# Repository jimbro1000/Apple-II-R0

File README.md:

# APPLE II R0 Reproduction #

## Goal
THe primary goal is to have an accurate KiCAD schematic of the 
Apple II Revision 0 System Board. This is supplemented with a
complete reproduction PCB that can be fabricated.

## Apple II R0 Notes

This schematic was taken from the [BitPreserve project](https://github.com/baldengineer/bit-preserve) and compared to the Apple II Gerbers by Mike Willegal (http://www.willegal.net/appleii/appleii-first_page.htm).
When necessary, The Apple II Circuit Description by Winston D. Gayler was consulted.

The PCB layout is a reworking of the Gerbers by Mike Willegal in 
KiCad. Where components are unobtainable from regular suppliers,
substitutes have been used with part number references.

## Current Status

1) Some errors have been found and corrected.
2) Additional work needs to be done to clean-up the schematic.
3) PCB is fully routed but needs mounting holes placing
4) Labelling (silkscreen) on the PCB is messy and needs cleaning up

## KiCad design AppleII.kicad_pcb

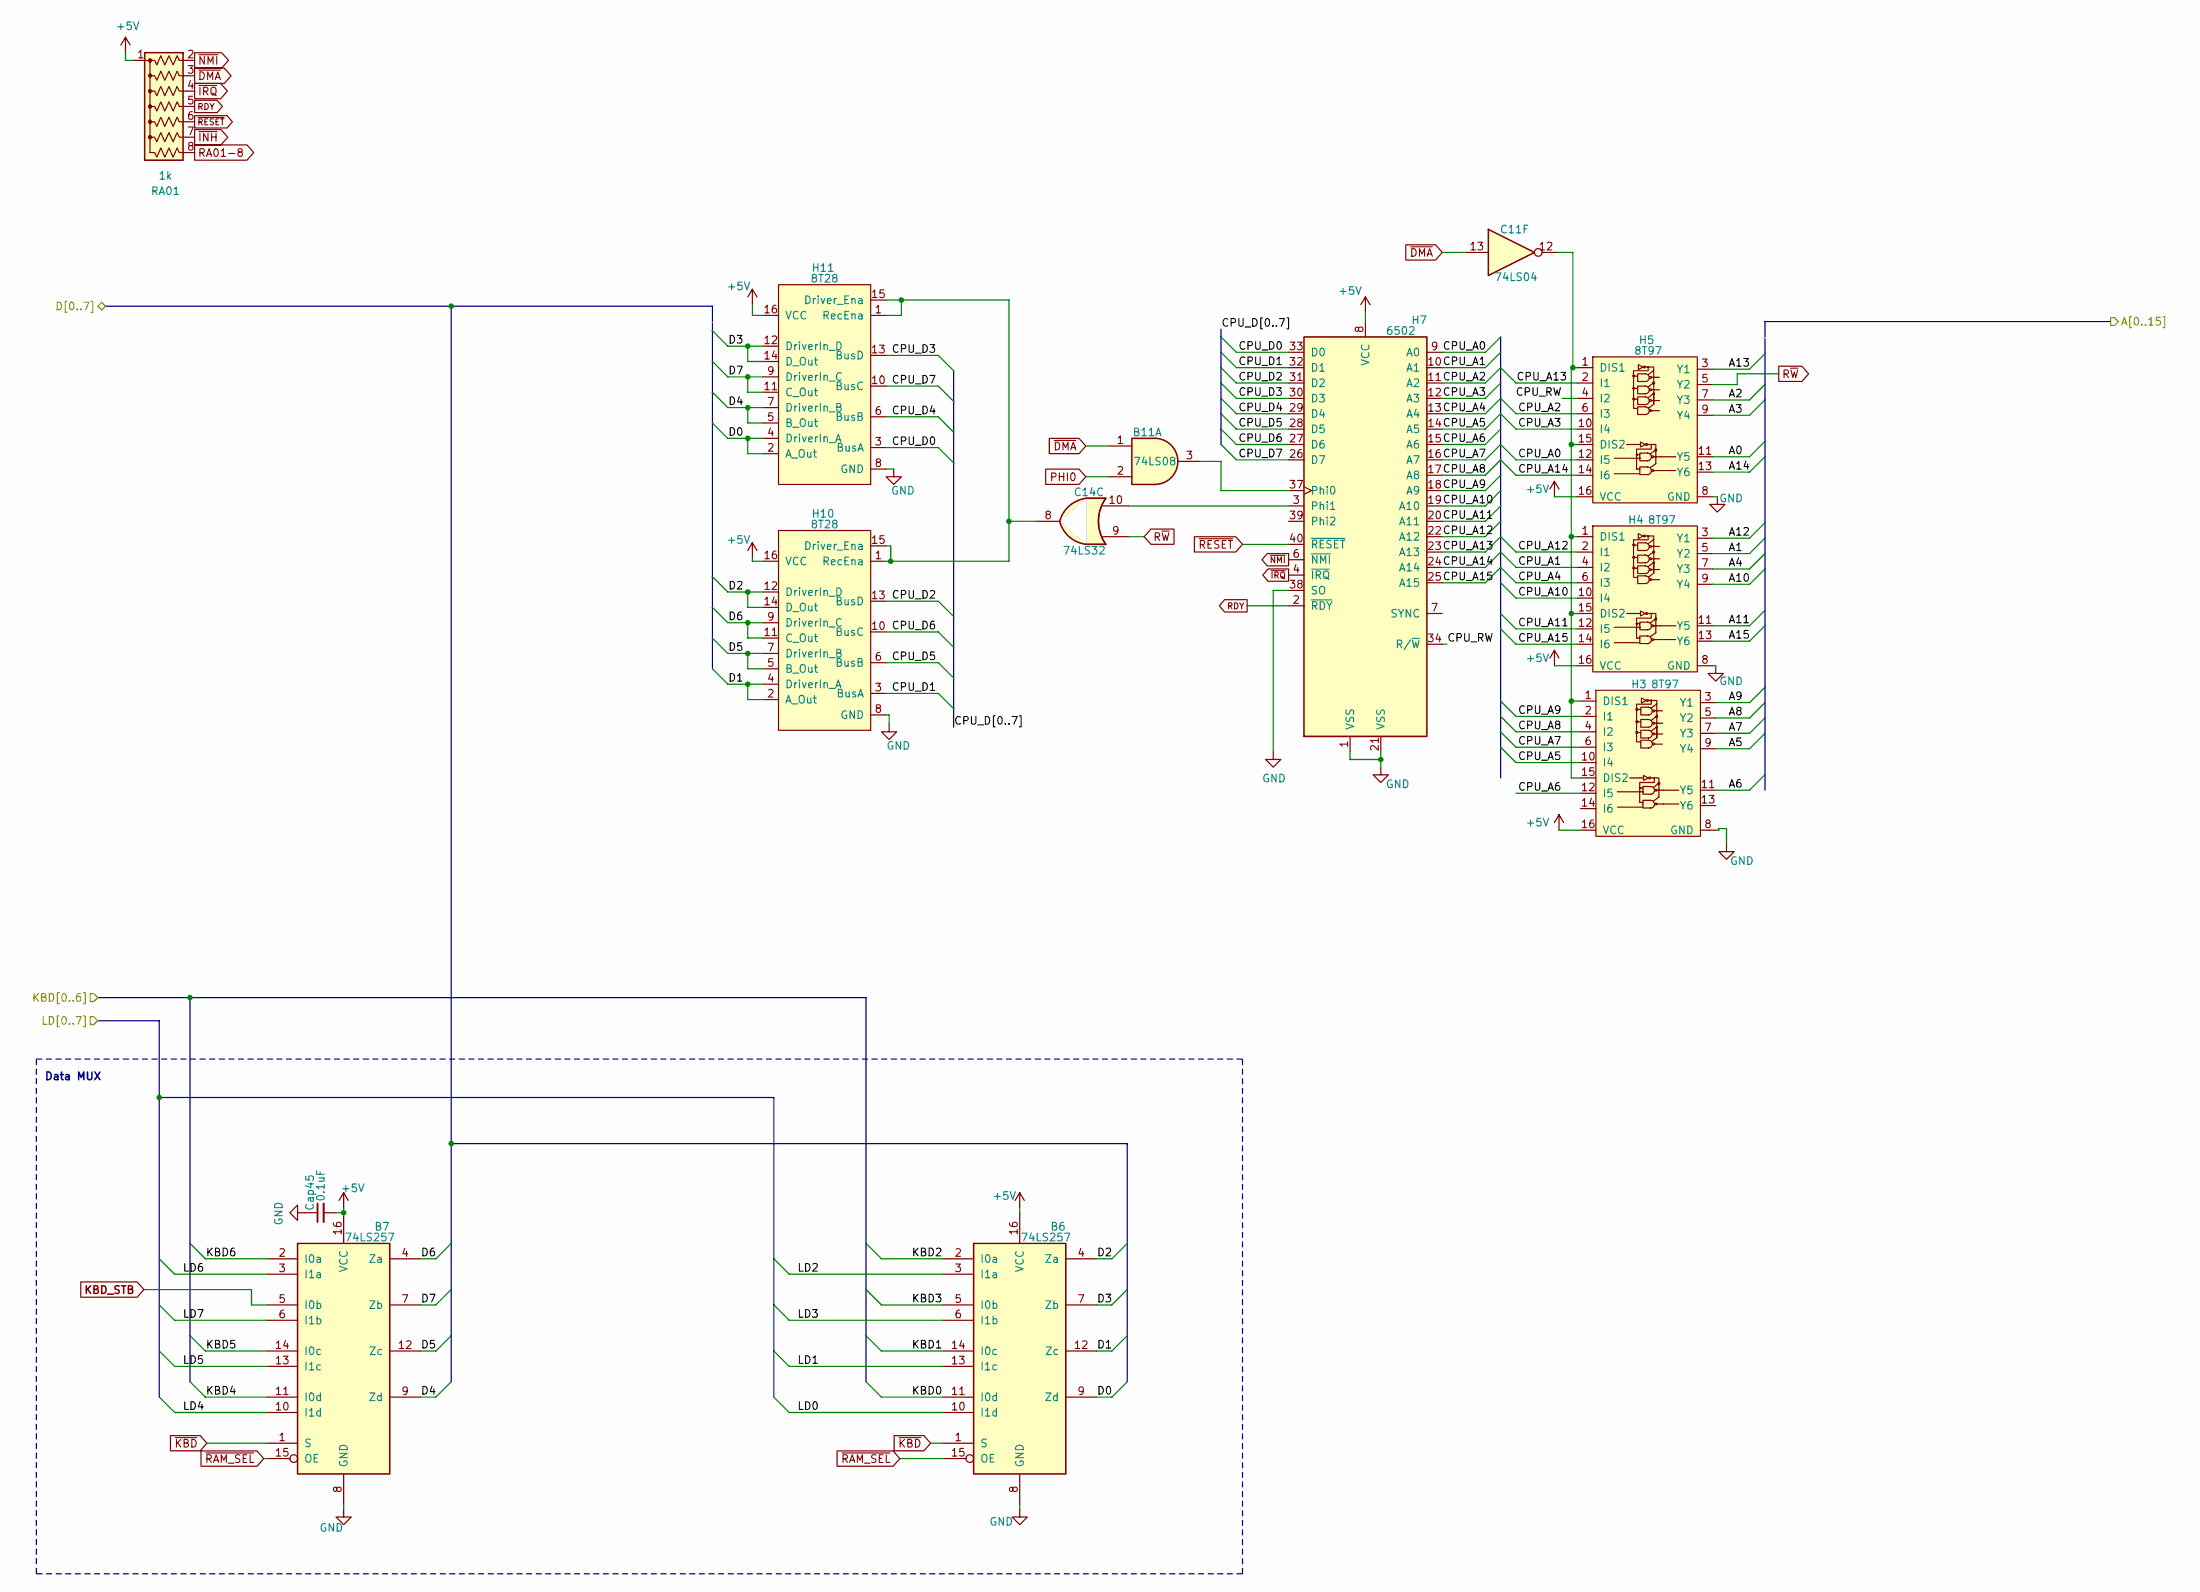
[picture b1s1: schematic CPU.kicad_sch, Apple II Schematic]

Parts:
B6, B7: 74LS257; DIP-16_W7.62mm
B11: 74LS08; DIP-14_W7.62mm
C11: 74LS04; DIP-14_W7.62mm
C14: 74LS32; DIP-14_W7.62mm
Cap45: 0.1uF; C_Disc_D5.0mm_W2.5mm_P5.00mm
H3, H4, H5: 8T97; DIP-16_W7.62mm
H7: 6502; DIP-40_W15.24mm
H10, H11: 8T28; DIP-16_W7.62mm
RA01: 1k; R_Array_SIP8

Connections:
+5V: B6.16 (VCC), B7.16 (VCC), Cap45.2, H3.16 (VCC), H4.16 (VCC), H5.16 (VCC), H7.8 (VCC), H10.16 (VCC), H11.16 (VCC), RA01.1 (common); also elsewhere on the board
/Address Decoder and Onboard IO/KBD0: B6.11 (I0d); also elsewhere on the board
/Address Decoder and Onboard IO/KBD1: B6.14 (I0c); also elsewhere on the board
/Address Decoder and Onboard IO/KBD2: B6.2 (I0a); also elsewhere on the board
/Address Decoder and Onboard IO/KBD3: B6.5 (I0b); also elsewhere on the board
/Address Decoder and Onboard IO/KBD4: B7.11 (I0d); also elsewhere on the board
/Address Decoder and Onboard IO/KBD5: B7.14 (I0c); also elsewhere on the board
/Address Decoder and Onboard IO/KBD6: B7.2 (I0a); also elsewhere on the board
/CPU Tranceiver Driver and Data MUX/CPU_A0: H5.12 (I5), H7.9 (A0)
/CPU Tranceiver Driver and Data MUX/CPU_A1: H4.4 (I2), H7.10 (A1)
/CPU Tranceiver Driver and Data MUX/CPU_A2: H5.6 (I3), H7.11 (A2)
/CPU Tranceiver Driver and Data MUX/CPU_A3: H5.10 (I4), H7.12 (A3)
/CPU Tranceiver Driver and Data MUX/CPU_A4: H4.6 (I3), H7.13 (A4)
/CPU Tranceiver Driver and Data MUX/CPU_A5: H3.10 (I4), H7.14 (A5)
/CPU Tranceiver Driver and Data MUX/CPU_A6: H3.12 (I5), H7.15 (A6)
/CPU Tranceiver Driver and Data MUX/CPU_A7: H3.6 (I3), H7.16 (A7)
/CPU Tranceiver Driver and Data MUX/CPU_A8: H3.4 (I2), H7.17 (A8)
/CPU Tranceiver Driver and Data MUX/CPU_A9: H3.2 (I1), H7.18 (A9)
/CPU Tranceiver Driver and Data MUX/CPU_A10: H4.10 (I4), H7.19 (A10)
/CPU Tranceiver Driver and Data MUX/CPU_A11: H4.12 (I5), H7.20 (A11)
/CPU Tranceiver Driver and Data MUX/CPU_A12: H4.2 (I1), H7.22 (A12)
/CPU Tranceiver Driver and Data MUX/CPU_A13: H5.2 (I1), H7.23 (A13)
/CPU Tranceiver Driver and Data MUX/CPU_A14: H5.14 (I6), H7.24 (A14)
/CPU Tranceiver Driver and Data MUX/CPU_A15: H4.14 (I6), H7.25 (A15)
/CPU Tranceiver Driver and Data MUX/CPU_D0: H7.33 (D0), H11.3 (BusA)
/CPU Tranceiver Driver and Data MUX/CPU_D1: H7.32 (D1), H10.3 (BusA)
/CPU Tranceiver Driver and Data MUX/CPU_D2: H7.31 (D2), H10.13 (BusD)
/CPU Tranceiver Driver and Data MUX/CPU_D3: H7.30 (D3), H11.13 (BusD)
/CPU Tranceiver Driver and Data MUX/CPU_D4: H7.29 (D4), H11.6 (BusB)
/CPU Tranceiver Driver and Data MUX/CPU_D5: H7.28 (D5), H10.6 (BusB)
/CPU Tranceiver Driver and Data MUX/CPU_D6: H7.27 (D6), H10.10 (BusC)
/CPU Tranceiver Driver and Data MUX/CPU_D7: H7.26 (D7), H11.10 (BusC)
/CPU Tranceiver Driver and Data MUX/CPU_RW: H5.4 (I2), H7.34 (R/~W)
/CPU Tranceiver Driver and Data MUX/LD0: B6.10 (I1d); also elsewhere on the board
/CPU Tranceiver Driver and Data MUX/LD1: B6.13 (I1c); also elsewhere on the board
/CPU Tranceiver Driver and Data MUX/LD2: B6.3 (I1a); also elsewhere on the board
/CPU Tranceiver Driver and Data MUX/LD3: B6.6 (I1b); also elsewhere on the board
/CPU Tranceiver Driver and Data MUX/LD4: B7.10 (I1d); also elsewhere on the board
/CPU Tranceiver Driver and Data MUX/LD5: B7.13 (I1c); also elsewhere on the board
/CPU Tranceiver Driver and Data MUX/LD6: B7.3 (I1a); also elsewhere on the board
/CPU Tranceiver Driver and Data MUX/LD7: B7.6 (I1b); also elsewhere on the board
A0: H5.11 (Y5); also elsewhere on the board
A1: H4.5 (Y2); also elsewhere on the board
A2: H5.7 (Y3); also elsewhere on the board
A3: H5.9 (Y4); also elsewhere on the board
A4: H4.7 (Y3); also elsewhere on the board
A5: H3.9 (Y4); also elsewhere on the board
A6: H3.11 (Y5); also elsewhere on the board
A7: H3.7 (Y3); also elsewhere on the board
A8: H3.5 (Y2); also elsewhere on the board
A9: H3.3 (Y1); also elsewhere on the board
A10: H4.9 (Y4); also elsewhere on the board
A11: H4.11 (Y5); also elsewhere on the board
A12: H4.3 (Y1); also elsewhere on the board
A13: H5.3 (Y1); also elsewhere on the board
A14: H5.13 (Y6); also elsewhere on the board
A15: H4.13 (Y6); also elsewhere on the board
D0: B6.9 (Zd), H11.2 (A_Out), H11.4 (DriverIn_A); also elsewhere on the board
D1: B6.12 (Zc), H10.2 (A_Out), H10.4 (DriverIn_A); also elsewhere on the board
D2: B6.4 (Za), H10.12 (DriverIn_D), H10.14 (D_Out); also elsewhere on the board
D3: B6.7 (Zb), H11.12 (DriverIn_D), H11.14 (D_Out); also elsewhere on the board
D4: B7.9 (Zd), H11.5 (B_Out), H11.7 (DriverIn_B); also elsewhere on the board
D5: B7.12 (Zc), H10.5 (B_Out), H10.7 (DriverIn_B); also elsewhere on the board
D6: B7.4 (Za), H10.9 (DriverIn_C), H10.11 (C_Out); also elsewhere on the board
D7: B7.7 (Zb), H11.9 (DriverIn_C), H11.11 (C_Out); also elsewhere on the board
GND: B6.8 (GND), B7.8 (GND), Cap45.1, H3.8 (GND), H4.8 (GND), H5.8 (GND), H7.1 (VSS), H7.21 (VSS), H7.38 (SO), H10.8 (GND), H11.8 (GND); also elsewhere on the board
KBD_STB: B7.5 (I0b); also elsewhere on the board
unnamed: C11.12, H3.1 (DIS1), H3.15 (DIS2), H4.1 (DIS1), H4.15 (DIS2), H5.1 (DIS1), H5.15 (DIS2)
unnamed: B11.3, H7.37 (Phi0)
unnamed: C14.10, H7.3 (Phi1)
unnamed: C14.8, H10.1 (RecEna), H10.15 (Driver_Ena), H11.1 (RecEna), H11.15 (Driver_Ena)
PHI0: B11.2; also elsewhere on the board
RA01-8: RA01.8 (R7); also elsewhere on the board
RDY: H7.2 (~RDY), RA01.5 (R4); also elsewhere on the board
R~W: C14.9, H5.5 (Y2); also elsewhere on the board
~DMA: B11.1, C11.13, RA01.3 (R2); also elsewhere on the board
~INH: RA01.7 (R6); also elsewhere on the board
~IRQ: H7.4 (~IRQ), RA01.4 (R3); also elsewhere on the board
~KBD: B6.1 (S), B7.1 (S); also elsewhere on the board
~NMI: H7.6 (~NMI), RA01.2 (R1); also elsewhere on the board
~RAM_SEL: B6.15 (OE), B7.15 (OE); also elsewhere on the board
~RESET: H7.40 (~RESET), RA01.6 (R5); also elsewhere on the board

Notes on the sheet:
Data MUX

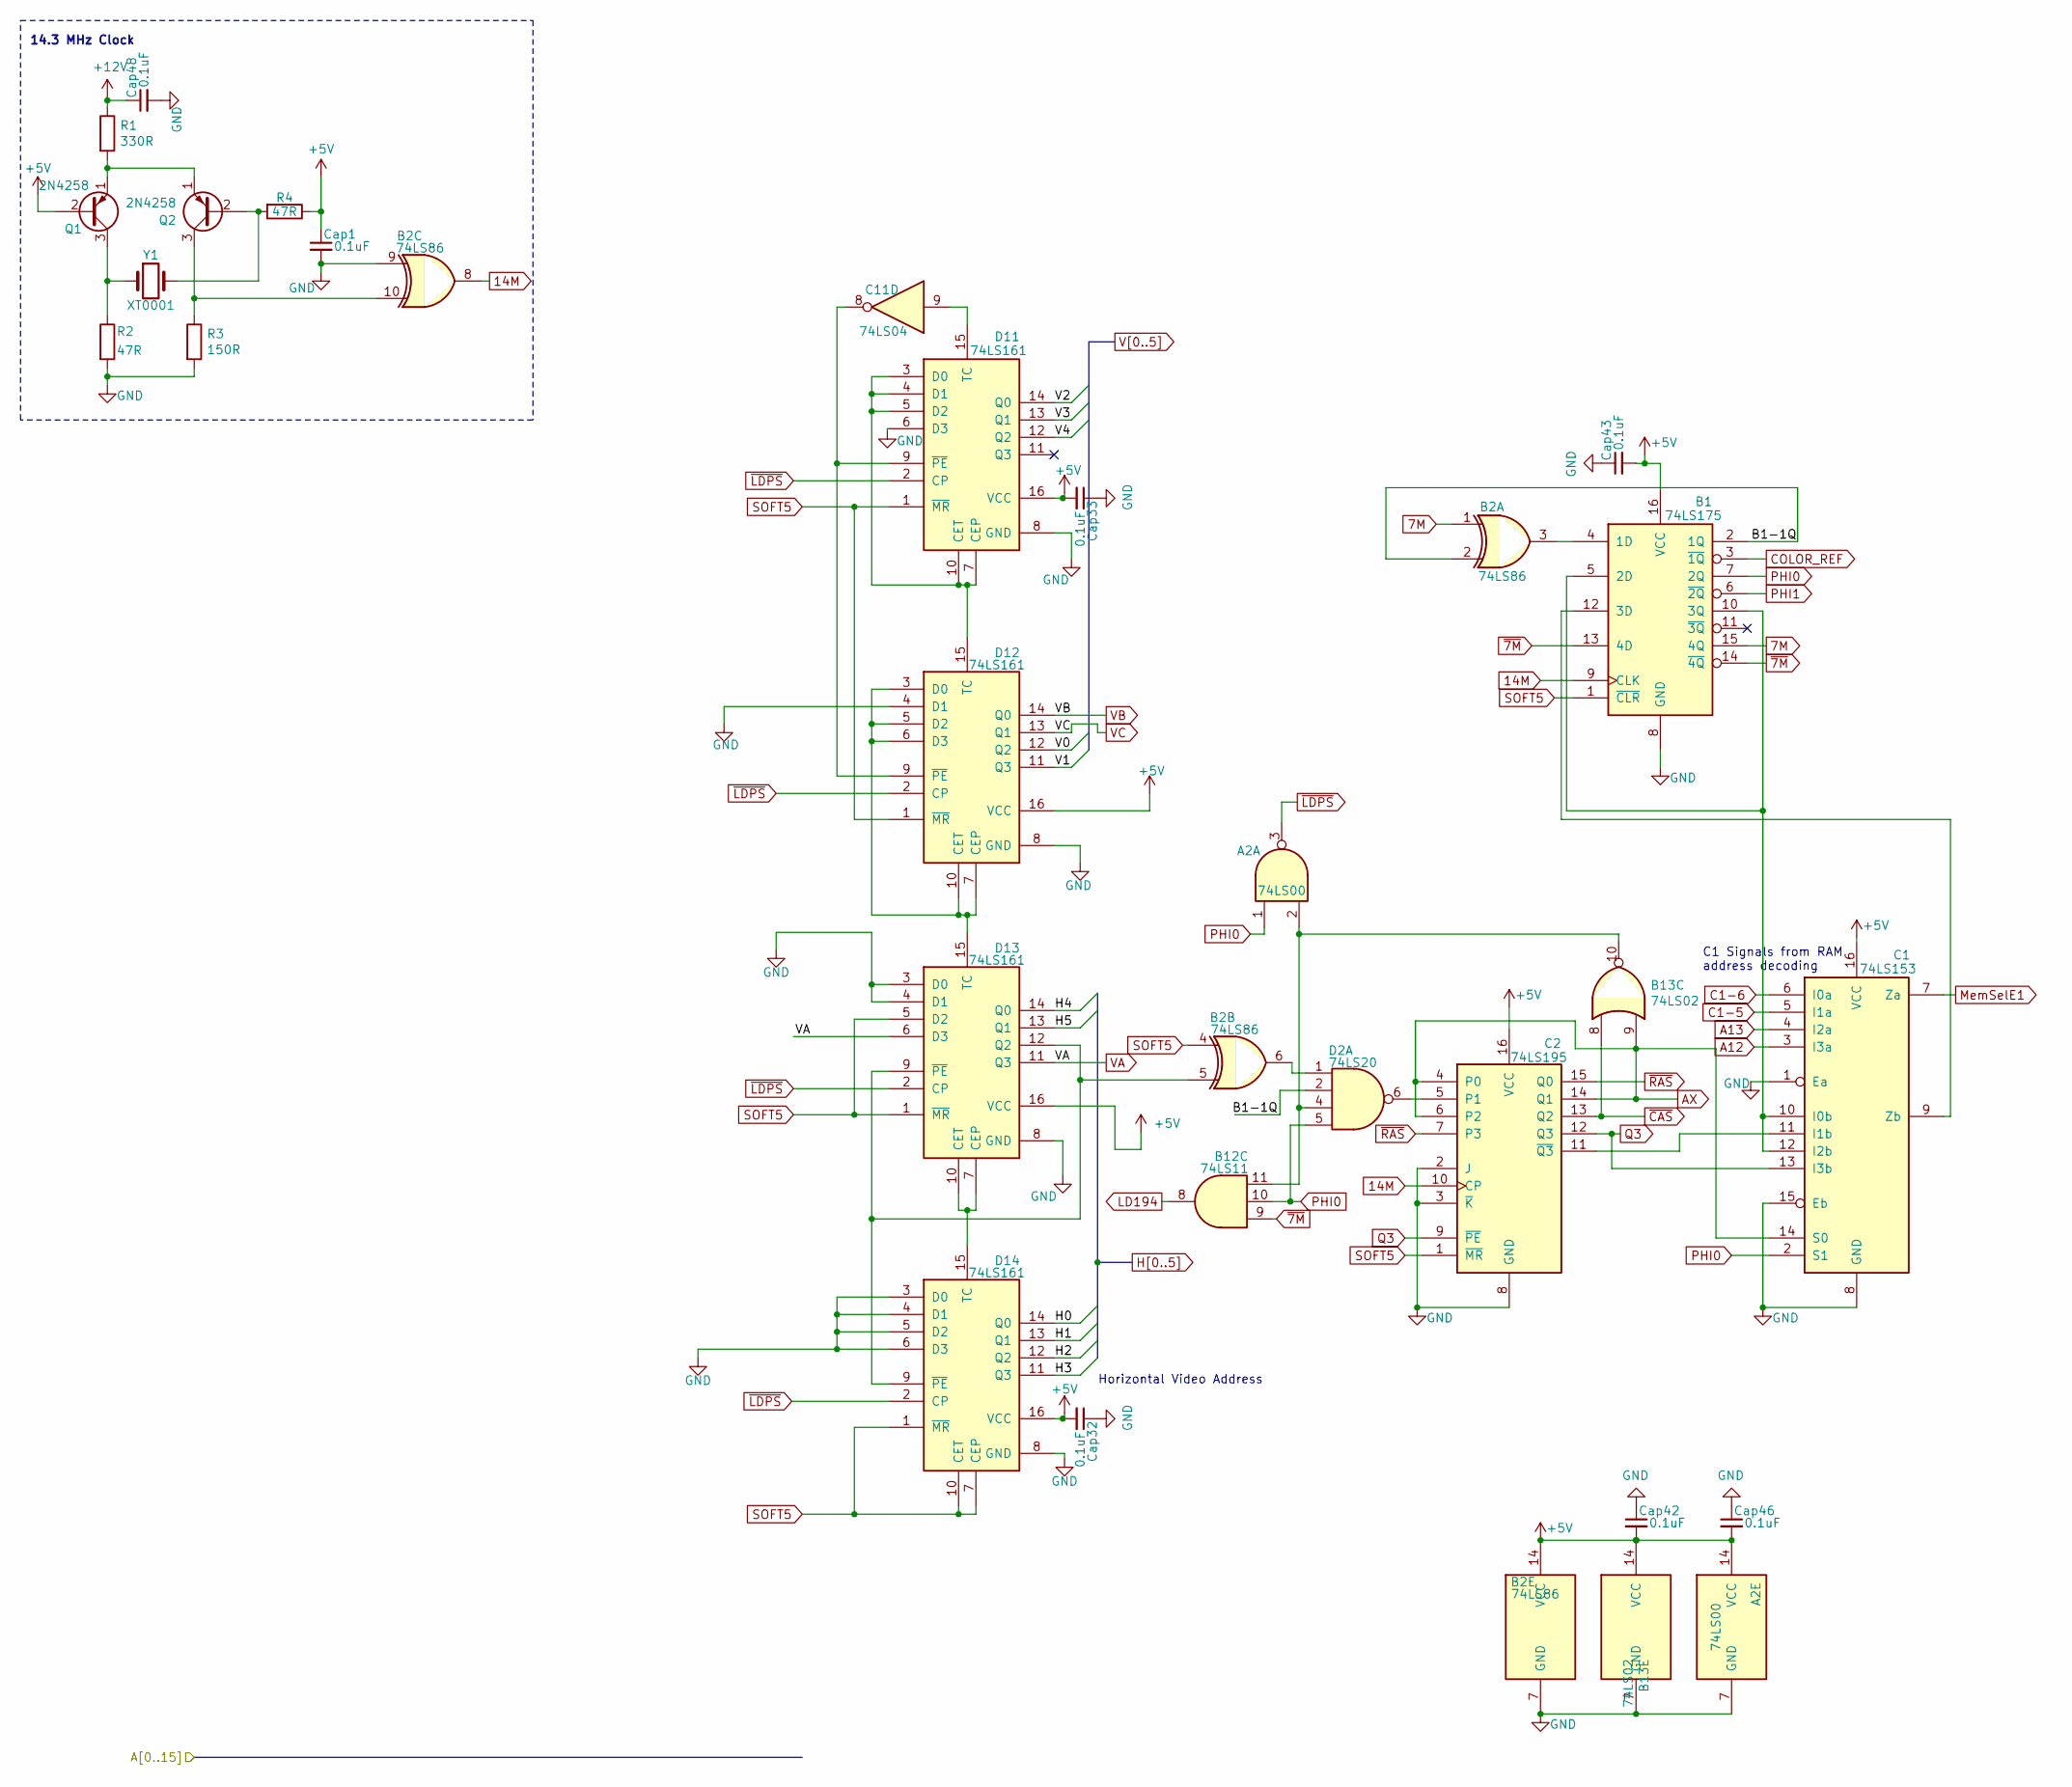
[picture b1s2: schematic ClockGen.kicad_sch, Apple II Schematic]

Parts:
A2: 74LS00; DIP-14_W7.62mm
B1: 74LS175; DIP-16_W7.62mm
B2: 74LS86; DIP-14_W7.62mm
B12: 74LS11; DIP-14_W7.62mm
B13: 74LS02; DIP-14_W7.62mm
C1: 74LS153; DIP-16_W7.62mm
C2: 74LS195; DIP-16_W7.62mm
C11: 74LS04; DIP-14_W7.62mm
Cap1, Cap32, Cap33, Cap42, Cap43, Cap46, Cap48: 0.1uF; C_Disc_D5.0mm_W2.5mm_P5.00mm
D2: 74LS20; DIP-14_W7.62mm
D11, D12, D13, D14: 74LS161; DIP-16_W7.62mm
Q1, Q2: 2N4258; TO-18-3; DigiKey 2N4208-ND
R1: 330R; R_Axial_DIN0207_L6.3mm_D2.5mm_P10.16mm_Horizontal
R2, R4: 47R; R_Axial_DIN0207_L6.3mm_D2.5mm_P10.16mm_Horizontal
R3: 150R; R_Axial_DIN0207_L6.3mm_D2.5mm_P10.16mm_Horizontal
Y1: XT0001; Crystal_HC18-U_Vertical

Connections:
7M: B1.15 (4Q), B2.1; also elsewhere on the board
14M: B1.9 (CLK), B2.8, C2.10 (CP); also elsewhere on the board
+5V: A2.14 (VCC), B1.16 (VCC), B2.14 (VCC), B13.14 (VCC), C1.16 (VCC), C2.16 (VCC), Cap1.1, Cap32.2, Cap33.2, Cap42.2, Cap43.2, Cap46.2, D11.16 (VCC), D12.16 (VCC), D13.16 (VCC), D14.16 (VCC), Q1.2 (B), R4.1; also elsewhere on the board
+12V: Cap48.1, R1.1; also elsewhere on the board
/Clock Generation/B1-1Q: B1.2 (1Q), B2.2, D2.2
/Clock Generation/H0: D14.14 (Q0); also elsewhere on the board
/Clock Generation/H1: D14.13 (Q1); also elsewhere on the board
/Clock Generation/H2: D14.12 (Q2); also elsewhere on the board
/Clock Generation/H3: D14.11 (Q3); also elsewhere on the board
/Clock Generation/H4: D13.14 (Q0); also elsewhere on the board
/Clock Generation/H5: D13.13 (Q1); also elsewhere on the board
/Clock Generation/V1: D12.11 (Q3); also elsewhere on the board
/Clock Generation/V2: D11.14 (Q0); also elsewhere on the board
/Clock Generation/V3: D11.13 (Q1); also elsewhere on the board
/Clock Generation/V4: D11.12 (Q2); also elsewhere on the board
A12: C1.3 (I3a); also elsewhere on the board
A13: C1.4 (I2a); also elsewhere on the board
AX: B13.9, C1.14 (S0), C2.4 (P0), C2.6 (P2), C2.14 (Q1); also elsewhere on the board
C1-5: C1.5 (I1a); also elsewhere on the board
C1-6: C1.6 (I0a); also elsewhere on the board
COLOR_REF: B1.3 (~1Q); also elsewhere on the board
GND: A2.7 (GND), B1.8 (GND), B2.7 (GND), B2.9, B13.7 (GND), C1.1 (Ea), C1.8 (GND), C1.15 (Eb), C2.2 (J), C2.3 (~K), C2.8 (GND), Cap1.2, Cap32.1, Cap33.1, Cap42.1, Cap43.1, Cap46.1, Cap48.2, D11.6 (D3), D11.8 (GND), D12.4 (D1), D12.8 (GND), D13.3 (D0), D13.4 (D1), D13.8 (GND), D14.3 (D0), D14.4 (D1), D14.5 (D2), D14.6 (D3), D14.8 (GND), R2.2, R3.2; also elsewhere on the board
LD194: B12.8; also elsewhere on the board
MemSelE1: C1.7 (Za); also elsewhere on the board
unnamed: A2.2, B12.11, B13.10, D2.4
unnamed: B1.4 (1D), B2.3
unnamed: B1.5 (2D), B1.10 (3Q), C1.10 (I0b), C1.12 (I2b)
unnamed: B1.12 (3D), C1.9 (Zb)
unnamed: B2.6, D2.1
unnamed: C1.11 (I1b), C2.11 (~Q3)
unnamed: C2.5 (P1), D2.6
unnamed: D11.3 (D0), D11.4 (D1), D11.5 (D2), D11.7 (CEP), D11.10 (CET), D12.15 (TC)
unnamed: C11.9, D11.15 (TC)
unnamed: C11.8, D11.9 (~PE), D12.9 (~PE)
unnamed: D12.3 (D0), D12.5 (D2), D12.6 (D3), D12.7 (CEP), D12.10 (CET), D13.15 (TC)
unnamed: D13.7 (CEP), D13.10 (CET), D14.15 (TC)
unnamed: B2.5, D13.9 (~PE), D13.12 (Q2), D14.9 (~PE)
unnamed: Q1.3 (C), R2.1, Y1.1
unnamed: Q1.1 (E), Q2.1 (E), R1.2
unnamed: Q2.2 (B), R4.2, Y1.2
unnamed: B2.10, Q2.3 (C), R3.1
PHI0: A2.1, B1.7 (2Q), B12.10, C1.2 (S1), D2.5; also elsewhere on the board
PHI1: B1.6 (~2Q); also elsewhere on the board
Q3: C1.13 (I3b), C2.9 (~PE), C2.12 (Q3); also elsewhere on the board
SOFT5: B1.1 (~CLR), B2.4, C2.1 (~MR), D11.1 (~MR), D12.1 (~MR), D13.1 (~MR), D13.5 (D2), D14.1 (~MR), D14.7 (CEP), D14.10 (CET); also elsewhere on the board
V0: D12.12 (Q2); also elsewhere on the board
VA: D13.6 (D3), D13.11 (Q3); also elsewhere on the board
VB: D12.14 (Q0); also elsewhere on the board
VC: D12.13 (Q1); also elsewhere on the board
~7M: B1.13 (4D), B1.14 (~4Q), B12.9; also elsewhere on the board
~CAS: B13.8, C2.13 (Q2); also elsewhere on the board
~LDPS: A2.3, D11.2 (CP), D12.2 (CP), D13.2 (CP), D14.2 (CP); also elsewhere on the board
~RAS: C2.7 (P3), C2.15 (Q0); also elsewhere on the board

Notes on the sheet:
Horizontal Video Address
14.3 MHz Clock
C1 Signals from RAM address decoding

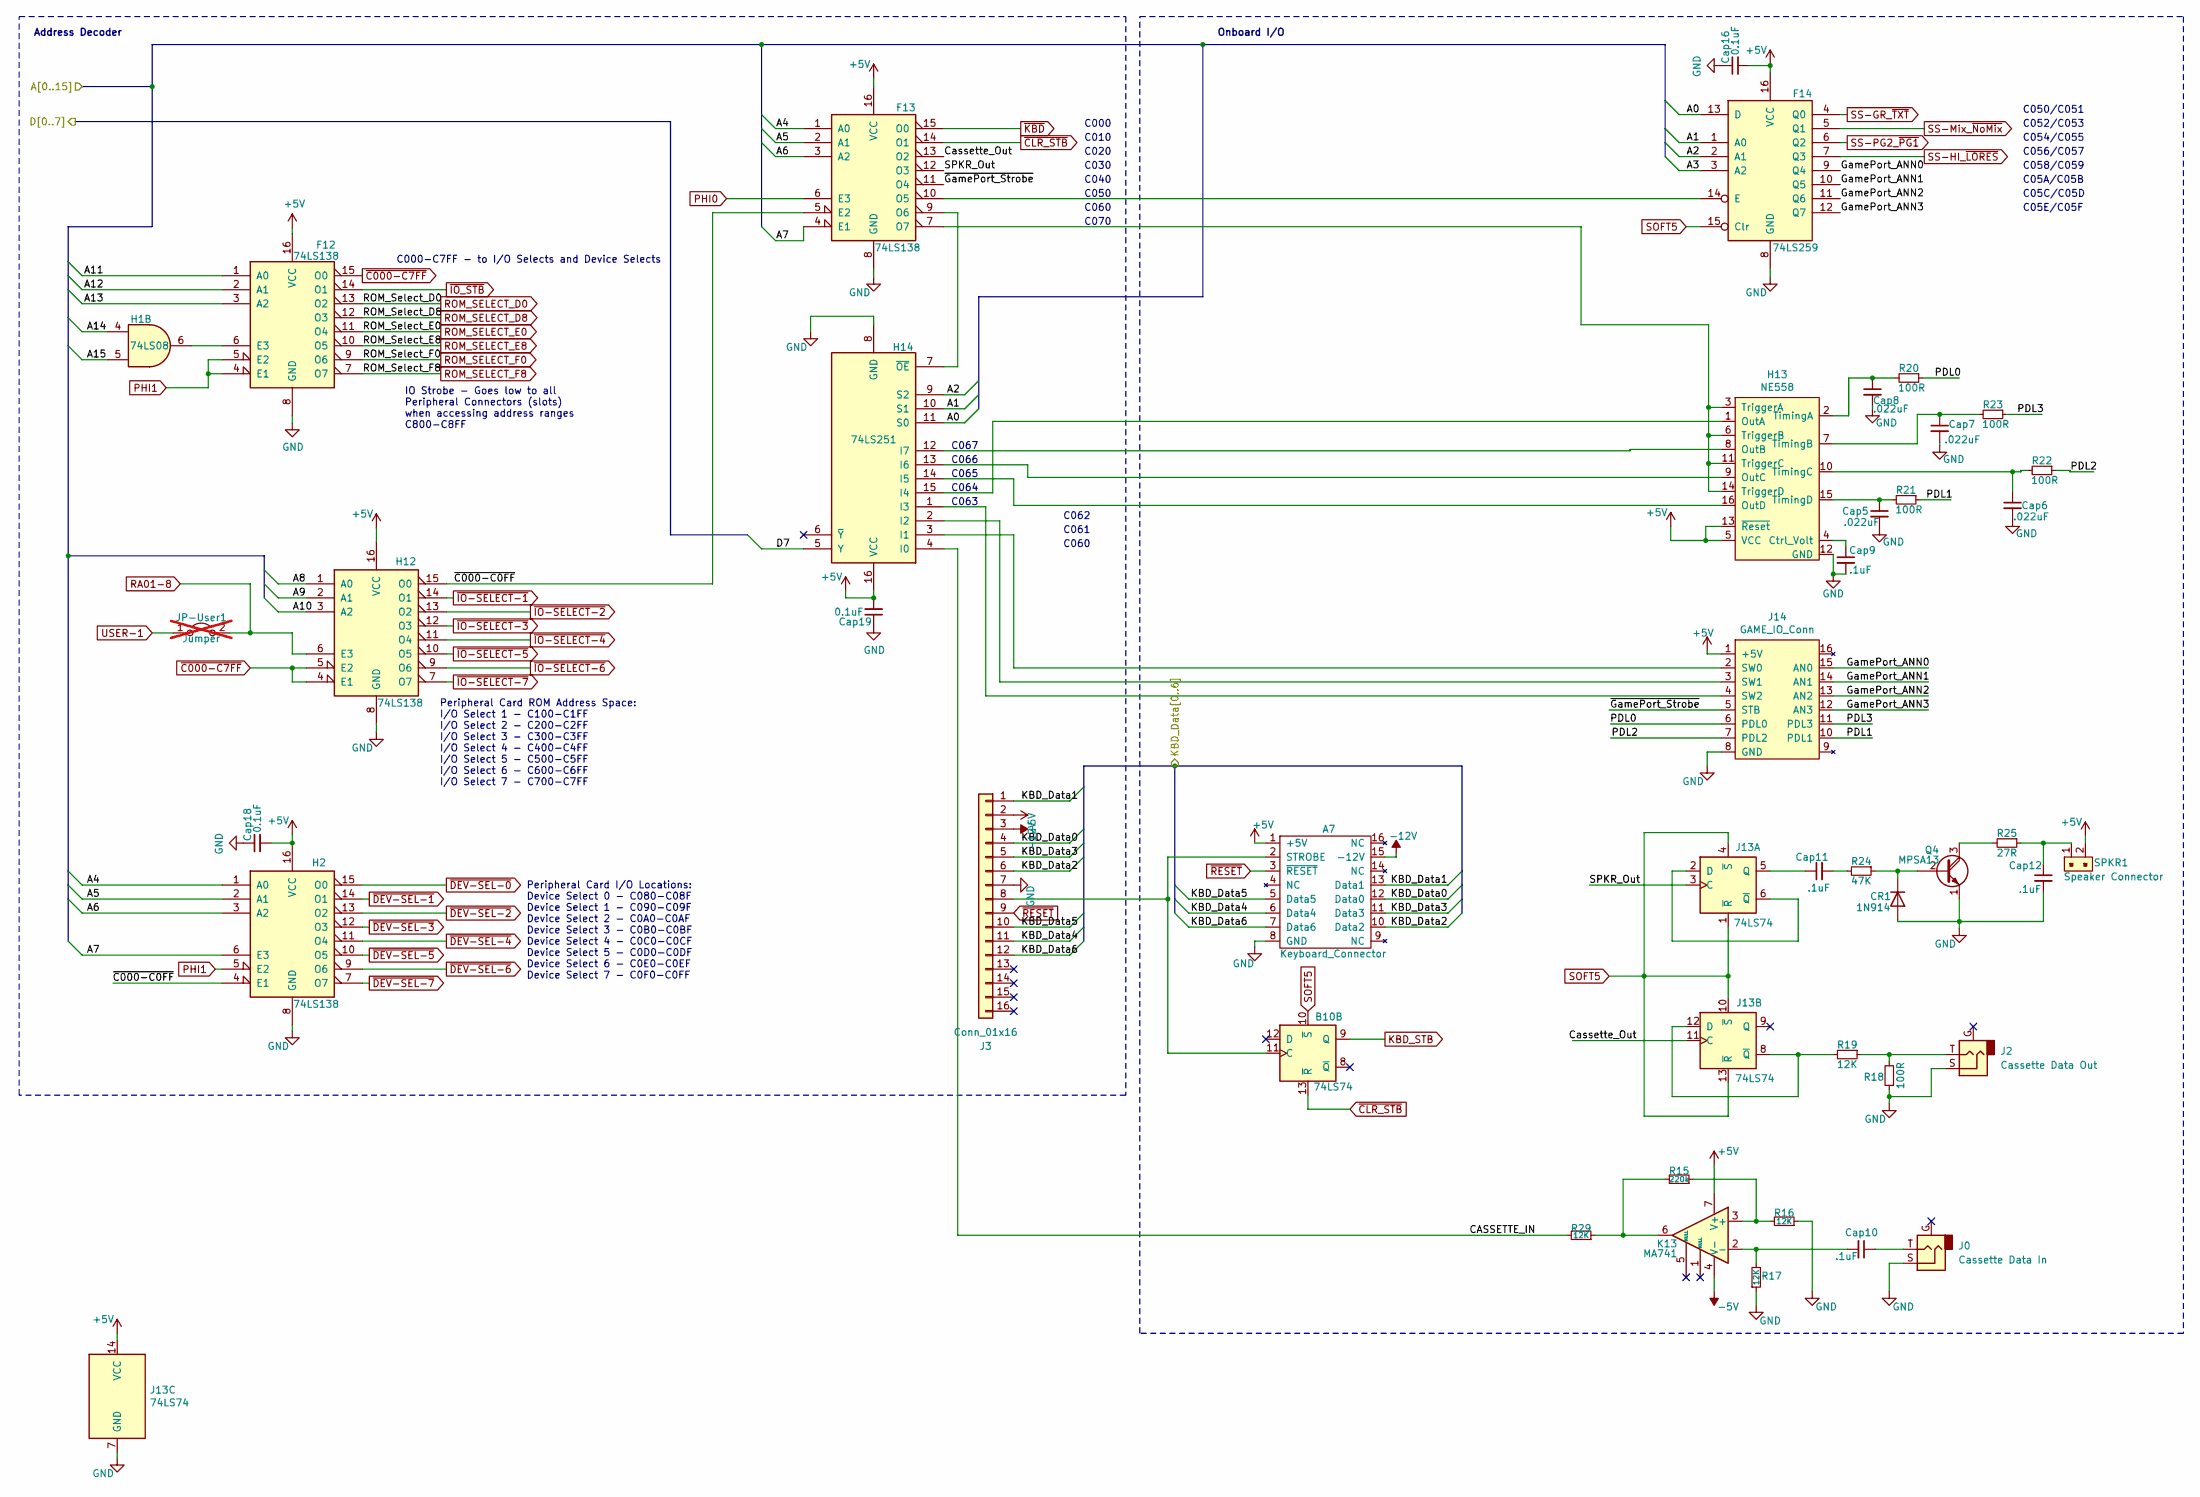
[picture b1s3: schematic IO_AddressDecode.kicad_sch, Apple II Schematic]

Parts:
A7: Keyboard_Connector; DIP-16_W7.62mm_Socket_LongPads
B10: 74LS74; DIP-14_W7.62mm
CR1: 1N914; D_DO-15_P10.16mm_Horizontal
Cap5, Cap6, Cap7, Cap8: .022uF; C_Disc_D5.0mm_W2.5mm_P5.00mm
Cap9, Cap10, Cap11, Cap12: .1uF; C_Disc_D5.0mm_W2.5mm_P5.00mm
Cap16, Cap18, Cap19: 0.1uF; C_Disc_D5.0mm_W2.5mm_P5.00mm
F12, F13: 74LS138; DIP-16_W7.62mm
F14: 74LS259; DIP-16_W7.62mm
H1: 74LS08; DIP-14_W7.62mm
H2, H12: 74LS138; DIP-16_W7.62mm
H13: NE558; DIP-16_W7.62mm
H14: 74LS251; DIP-16_W7.62mm
J0: Cassette Data In; AUDIO_mono; DigiKey CP-3502N-ND
J2: Cassette Data Out; AUDIO_mono; DigiKey CP-3502N-ND
J3: Conn_01x16; PinHeader_1x16_P2.54mm_Vertical
J13: 74LS74; DIP-14_W7.62mm
J14: GAME_IO_Conn; DIP-16_W7.62mm_Socket_LongPads
JP-User1: Jumper; PinSocket_1x02_P2.54mm_Vertical; not fitted
K13: MA741; DIP-8_W7.62mm
Q4: MPSA13; TO-92; DigiKey KSP13BU-ND
R15: 220k; R_Axial_DIN0207_L6.3mm_D2.5mm_P10.16mm_Horizontal
R16, R17, R19, R29: 12K; R_Axial_DIN0207_L6.3mm_D2.5mm_P10.16mm_Horizontal
R18, R20, R21, R22, R23: 100R; R_Axial_DIN0207_L6.3mm_D2.5mm_P10.16mm_Horizontal
R24: 47K; R_Axial_DIN0207_L6.3mm_D2.5mm_P10.16mm_Horizontal
R25: 27R; R_Axial_DIN0207_L6.3mm_D2.5mm_P10.16mm_Horizontal
SPKR1: Speaker Connector; PinSocket_1x02_P2.54mm_Vertical; MPN 22-23-2021; Digi-Key_PN WM4200-ND

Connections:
+5V: A7.1 (+5V), Cap16.2, Cap18.2, Cap19.2, F12.16 (VCC), F13.16 (VCC), F14.16 (VCC), H2.16 (VCC), H12.16 (VCC), H13.5 (VCC), H13.13 (~Reset), H14.16 (VCC), J3.2, J13.14 (VCC), J14.1 (+5V), K13.7 (V+), SPKR1.2; also elsewhere on the board
-5V: K13.4 (V-); also elsewhere on the board
-12V: A7.15 (-12V), J3.3; also elsewhere on the board
/Address Decoder and Onboard IO/CASSETTE_IN: H14.4 (I0), R29.2
/Address Decoder and Onboard IO/Cassette_Out: F13.13 (O2), J13.11 (C)
/Address Decoder and Onboard IO/GamePort_ANN0: F14.9 (Q4), J14.15 (AN0)
/Address Decoder and Onboard IO/GamePort_ANN1: F14.10 (Q5), J14.14 (AN1)
/Address Decoder and Onboard IO/GamePort_ANN2: F14.11 (Q6), J14.13 (AN2)
/Address Decoder and Onboard IO/GamePort_ANN3: F14.12 (Q7), J14.12 (AN3)
/Address Decoder and Onboard IO/KBD0: A7.12 (Data0), J3.4; also elsewhere on the board
/Address Decoder and Onboard IO/KBD1: A7.13 (Data1), J3.1; also elsewhere on the board
/Address Decoder and Onboard IO/KBD2: A7.10 (Data2), J3.6; also elsewhere on the board
/Address Decoder and Onboard IO/KBD3: A7.11 (Data3), J3.5; also elsewhere on the board
/Address Decoder and Onboard IO/KBD4: A7.6 (Data4), J3.11; also elsewhere on the board
/Address Decoder and Onboard IO/KBD5: A7.5 (Data5), J3.10; also elsewhere on the board
/Address Decoder and Onboard IO/KBD6: A7.7 (Data6), J3.12; also elsewhere on the board
/Address Decoder and Onboard IO/PDL0: J14.6 (PDL0), R20.1
/Address Decoder and Onboard IO/PDL1: J14.10 (PDL1), R21.1
/Address Decoder and Onboard IO/PDL2: J14.7 (PDL2), R22.1
/Address Decoder and Onboard IO/PDL3: J14.11 (PDL3), R23.1
/Address Decoder and Onboard IO/SPKR_Out: F13.12 (O3), J13.3 (C)
/Address Decoder and Onboard IO/~C000-C0FF: F13.5 (E2), H2.4 (E1), H12.15 (O0)
/Address Decoder and Onboard IO/~GamePort_Strobe: F13.11 (O4), J14.5 (STB)
A0: F14.13 (D), H14.11 (S0); also elsewhere on the board
A1: F14.1 (A0), H14.10 (S1); also elsewhere on the board
A2: F14.2 (A1), H14.9 (S2); also elsewhere on the board
A3: F14.3 (A2); also elsewhere on the board
A4: F13.1 (A0), H2.1 (A0); also elsewhere on the board
A5: F13.2 (A1), H2.2 (A1); also elsewhere on the board
A6: F13.3 (A2), H2.3 (A2); also elsewhere on the board
A7: F13.4 (E1), H2.6 (E3); also elsewhere on the board
A8: H12.1 (A0); also elsewhere on the board
A9: H12.2 (A1); also elsewhere on the board
A10: H12.3 (A2); also elsewhere on the board
A11: F12.1 (A0); also elsewhere on the board
A12: F12.2 (A1); also elsewhere on the board
A13: F12.3 (A2); also elsewhere on the board
A14: H1.4; also elsewhere on the board
A15: H1.5; also elsewhere on the board
D7: H14.5 (Y); also elsewhere on the board
GND: A7.8 (GND), CR1.2 (A), Cap5.2, Cap6.2, Cap7.2, Cap8.2, Cap9.2, Cap12.2, Cap16.1, Cap18.1, Cap19.1, F12.8 (GND), F13.8 (GND), F14.8 (GND), H2.8 (GND), H12.8 (GND), H13.12 (GND), H14.8 (GND), J0.S, J2.S, J3.7, J13.7 (GND), J14.8 (GND), Q4.1 (E), R16.1, R17.1, R18.1; also elsewhere on the board
KBD_STB: B10.9 (Q); also elsewhere on the board
unnamed: A7.2 (STROBE), B10.11 (C), J3.8
unnamed: CR1.1 (K), Q4.2 (B), R24.1
unnamed: Cap10.1, J0.T
unnamed: Cap11.2, R24.2
unnamed: Cap12.1, R25.1, SPKR1.1
unnamed: F12.6 (E3), H1.6
unnamed: F13.10 (O5), F14.14 (E)
unnamed: F13.9 (O6), H14.7 (~OE)
unnamed: F13.7 (O7), H13.3 (TriggerA), H13.6 (TriggerB), H13.11 (TriggerC), H13.14 (TriggerD)
unnamed: Cap9.1, H13.4 (Ctrl_Volt)
unnamed: H13.1 (OutA), H14.15 (I4)
unnamed: H13.8 (OutB), H14.12 (I7)
unnamed: H13.9 (OutC), H14.13 (I6)
unnamed: H13.16 (OutD), H14.14 (I5)
unnamed: Cap8.1, H13.2 (TimingA), R20.2
unnamed: Cap7.1, H13.7 (TimingB), R23.2
unnamed: Cap6.1, H13.10 (TimingC), R22.2
unnamed: Cap5.1, H13.15 (TimingD), R21.2
unnamed: H14.3 (I1), J14.2 (SW0)
unnamed: H14.2 (I2), J14.3 (SW1)
unnamed: H14.1 (I3), J14.4 (SW2)
unnamed: J2.T, R18.2, R19.1
unnamed: J13.2 (D), J13.6 (~Q)
unnamed: Cap11.1, J13.5 (Q)
unnamed: J13.8 (~Q), J13.12 (D), R19.2
unnamed: K13.3 (+), R15.1, R16.2
unnamed: Cap10.2, K13.2 (-), R17.2
unnamed: K13.6, R15.2, R29.1
unnamed: Q4.3 (C), R25.2
PHI0: F13.6 (E3); also elsewhere on the board
PHI1: F12.4 (E1), F12.5 (E2), H2.5 (E2); also elsewhere on the board
RA01-8: H12.6 (E3), JP-User1.2 (B); also elsewhere on the board
ROM_SELECT_D0: F12.13 (O2); also elsewhere on the board
ROM_SELECT_D8: F12.12 (O3); also elsewhere on the board
ROM_SELECT_E0: F12.11 (O4); also elsewhere on the board
ROM_SELECT_E8: F12.10 (O5); also elsewhere on the board
ROM_SELECT_F0: F12.9 (O6); also elsewhere on the board
ROM_SELECT_F8: F12.7 (O7); also elsewhere on the board
SOFT5: B10.10 (~S), F14.15 (Clr), J13.1 (~R), J13.4 (~S), J13.10 (~S), J13.13 (~R); also elsewhere on the board
SS-GR_~TXT: F14.4 (Q0); also elsewhere on the board
SS-HI_~LORES: F14.7 (Q3); also elsewhere on the board
SS-Mix_~NoMix: F14.5 (Q1); also elsewhere on the board
SS-PG2_~PG1: F14.6 (Q2); also elsewhere on the board
USER-1: JP-User1.1 (A); also elsewhere on the board
~C000-C7FF: F12.15 (O0), H12.4 (E1), H12.5 (E2)
~CLR_STB: B10.13 (~R), F13.14 (O1)
~DEV-SEL-0: H2.15 (O0); also elsewhere on the board
~DEV-SEL-1: H2.14 (O1); also elsewhere on the board
~DEV-SEL-2: H2.13 (O2); also elsewhere on the board
~DEV-SEL-3: H2.12 (O3); also elsewhere on the board
~DEV-SEL-4: H2.11 (O4); also elsewhere on the board
~DEV-SEL-5: H2.10 (O5); also elsewhere on the board
~DEV-SEL-6: H2.9 (O6); also elsewhere on the board
~DEV-SEL-7: H2.7 (O7); also elsewhere on the board
~IO-SELECT-1: H12.14 (O1); also elsewhere on the board
~IO-SELECT-2: H12.13 (O2); also elsewhere on the board
~IO-SELECT-3: H12.12 (O3); also elsewhere on the board
~IO-SELECT-4: H12.11 (O4); also elsewhere on the board
~IO-SELECT-5: H12.10 (O5); also elsewhere on the board
~IO-SELECT-6: H12.9 (O6); also elsewhere on the board
~IO-SELECT-7: H12.7 (O7); also elsewhere on the board
~IO_STB: F12.14 (O1); also elsewhere on the board
~KBD: F13.15 (O0); also elsewhere on the board
~RESET: A7.3 (~RESET), J3.9; also elsewhere on the board

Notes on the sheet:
C050/C051
C060
C05E/C05F
C063
C054/C055
C050
C070
C052/C053
IO Strobe - Goes low to all Peripheral Connectors (slots) when accessing address ranges C800-C8FF
C066
C010
C000
Onboard I/O
C061
C05A/C05B
Address Decoder
C062
C05C/C05D
C040
Peripheral Card I/O Locations: Device Select 0 - C080-C08F Device Select 1 - C090-C09F Device Select 2 - C0A0-C0AF Device Select 3 - C0B0-C0BF Device Select 4 - C0C0-C0CF Device Select 5 - C0D0-C0DF Device Select 6 - C0E0-C0EF Device Select 7 - C0F0-C0FF
C064
C030
C056/C057
C065
C058/C059
C000-C7FF - to I/O Selects and Device Selects
C067
C020
Peripheral Card ROM Address Space: I/O Select 1 - C100-C1FF I/O Select 2 - C200-C2FF I/O Select 3 - C300-C3FF I/O Select 4 - C400-C4FF I/O Select 5 - C500-C5FF I/O Select 6 - C600-C6FF I/O Select 7 - C700-C7FF
